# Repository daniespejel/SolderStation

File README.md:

# Solderstation

Barebones Atmega328 based Soldering station  
Firmware: https://github.com/fngstudios/SolderStation_Software

## Features  
*FTDI/Arduino programming port     
*Common soldering tip (with thermocouple) compatible  
*Uses MAX31856 for TC reading  
*Configurable TC type supports J,K,N,E,etc  
*Configurable LCD contrast  
*PID control Kp,Ki and Kd configurable via UI  
*Idle mode for longer tip life  
*Automatic switch-off  
*Arduino compatible 100% customizable  
*Uses any PSU up to 35v like common laptop PSUs (depends on your tip)  
*Can be used barebones (with no cabinet) or built inside custom cabinet  

## Images

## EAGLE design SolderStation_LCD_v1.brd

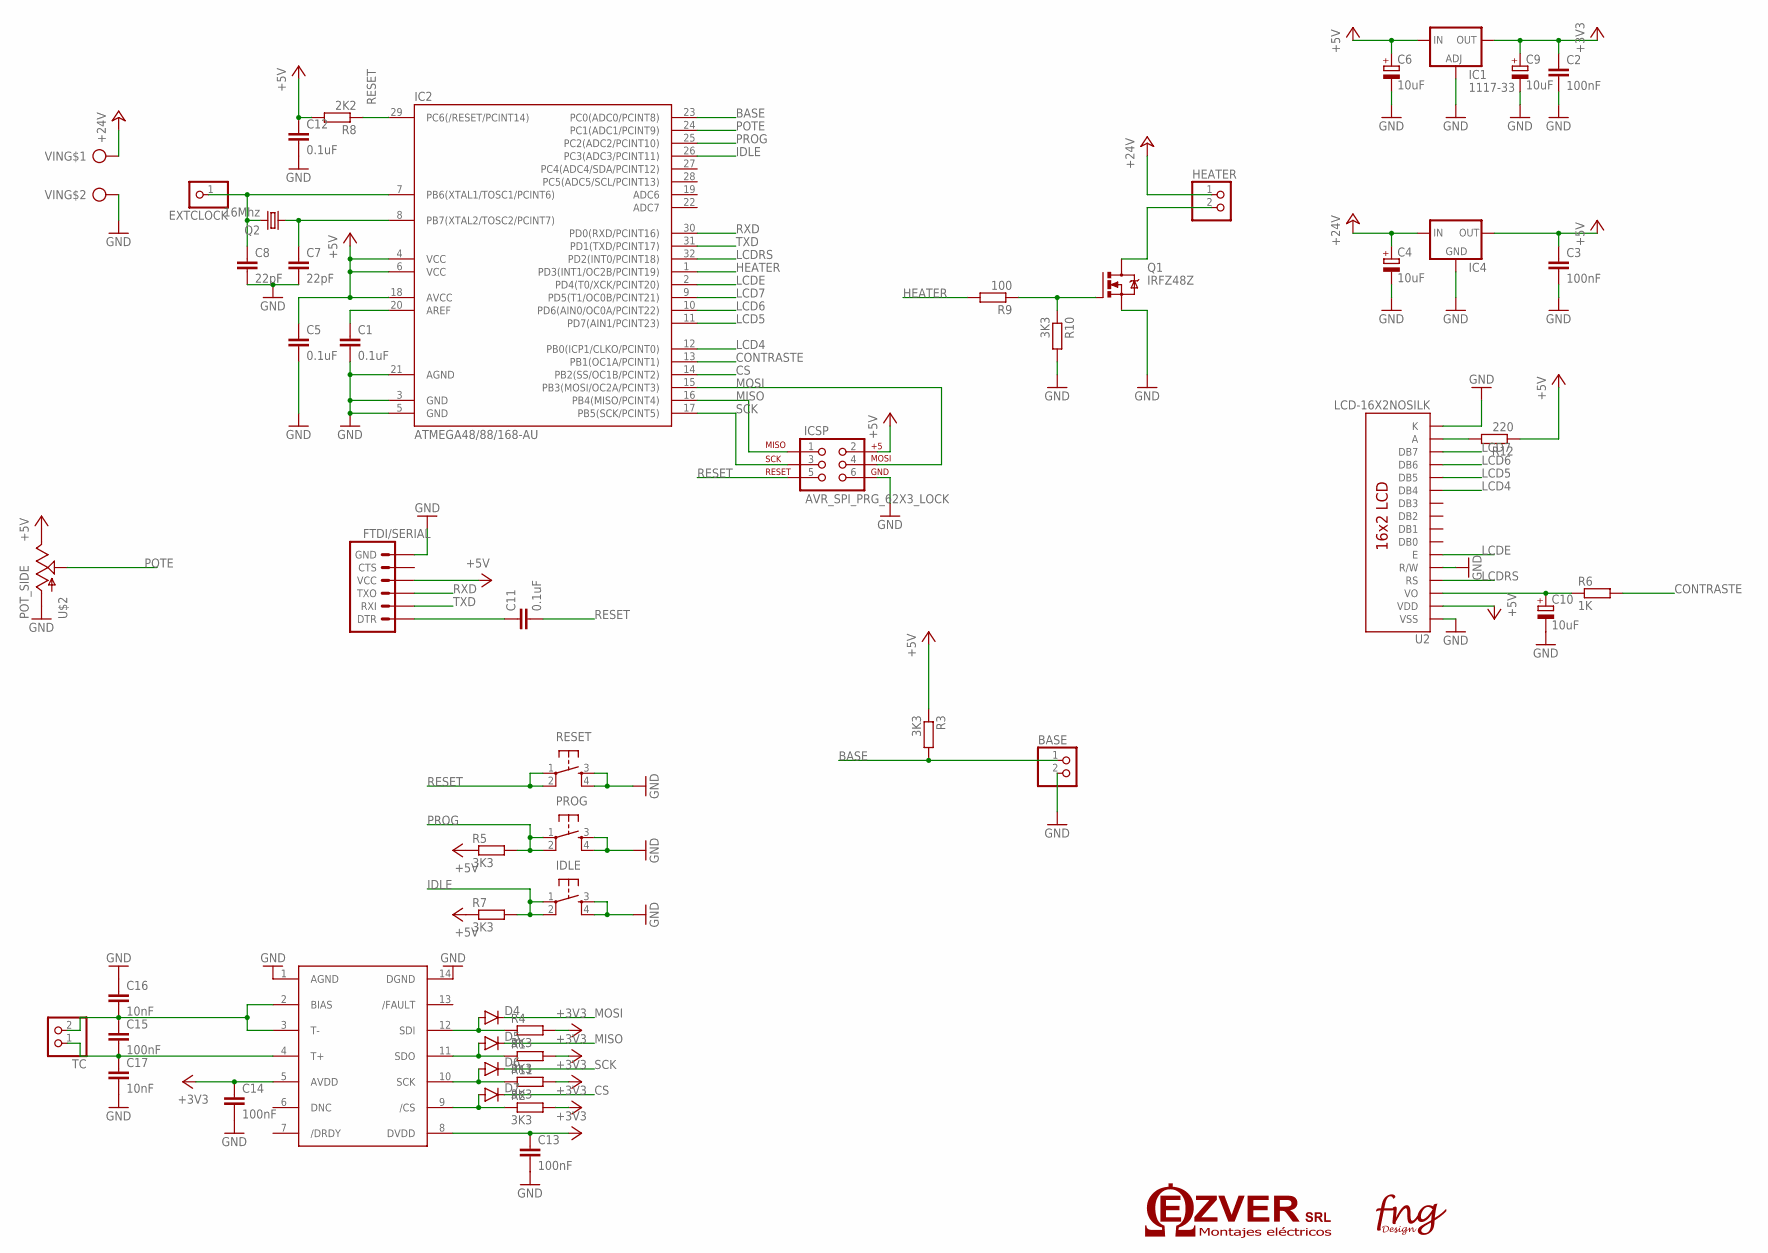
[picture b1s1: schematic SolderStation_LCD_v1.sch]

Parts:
BASE: PINHD-1X2; 1X02
C1, C5, C11, C12: 0.1uF; C1206K
C2, C3, C13, C14, C15: 100nF; C1206K
C4, C6, C9, C10: 10uF; CT3528
C7, C8: 22pF; C1206K
C16, C17: 10nF; C1206K
D4, D5, D6, D7: DIODESOD123; SOD-123
EXTCLOCK: PINHD-1X1; 1X01
FTDI/SERIAL: ARDUINO_SERIAL_PROGRAMLOCK; 1X06_LOCK
HEATER: PINHD-1X2; 1X02
IC1: 1117-33; DPACK
IC2: ATMEGA48/88/168-AU; TQFP32-08
IC4: 78XXL
ICSP: AVR_SPI_PRG_62X3_LOCK; 2X3_LOCK
IDLE: TAC_SWITCHPTH; TACTILE-PTH
PROG: TAC_SWITCHPTH; TACTILE-PTH
Q1: IRFZ48Z; TO220BH
Q2: 16Mhz; HC49U70
R1, R2, R3, R4, R5, R7, R10, R11: 3K3; M1206
R6: 1K; M1206
R8: 2K2; M1206
R9: 100; M1206
R12: 220; M1206
RESET: TAC_SWITCHPTH; TACTILE-PTH
TC: PINHD-1X2; 1X02
TC1: MAX31856; TSSOP-14
U2: LCD-16X2NOSILK; LCD-16X2_NOSILK
U$2: POT_SIDE; POT_ALPHA_SIDE
VIN: CON2

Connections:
+3V3: C2.1, C9.+, C13.1, C14.1, IC1.4 (OUT), R1.2, R2.2, R4.2, R11.2, TC1.5 (AVDD), TC1.8 (DVDD)
+5V: C3.1, C5.1, C6.+, C12.1, FTDI/SERIAL.4 (VCC), IC1.3 (IN), IC2.4 (VCC), IC2.6 (VCC), IC2.18 (AVCC), IC4.OUT, ICSP.2, R3.1, R5.1, R7.1, R8.2, R12.1, U2.2 (VDD), U$2.3 (E)
+24V: C4.+, HEATER.1, IC4.IN, VIN.1
BASE: BASE.1, IC2.23 (PC0(ADC0/PCINT8)), R3.2
CONTRASTE: IC2.13 (PB1(OC1A/PCINT1)), R6.2
CS: D7.C, IC2.14 (PB2(SS/OC1B/PCINT2))
GND: BASE.2, C1.2, C2.2, C3.2, C4.-, C5.2, C6.-, C7.2, C8.2, C9.-, C10.-, C12.2, C13.2, C14.2, C16.1, C17.2, FTDI/SERIAL.6 (GND), IC1.1 (ADJ), IC2.3 (GND), IC2.5 (GND), IC2.21 (AGND), IC4.GND, ICSP.6, IDLE.3, IDLE.4, PROG.3, PROG.4, Q1.S, R10.2, RESET.3, RESET.4, TC1.1 (AGND), TC1.14 (DGND), U2.1 (VSS), U2.5 (R/W), U2.16 (K), U$2.1 (A), VIN.2
HEATER: IC2.1 (PD3(INT1/OC2B/PCINT19)), R9.2
IDLE: IC2.26 (PC3(ADC3/PCINT11)), IDLE.1, IDLE.2, R7.2
LCD4: IC2.12 (PB0(ICP1/CLKO/PCINT0)), U2.11 (DB4)
LCD5: IC2.11 (PD7(AIN1/PCINT23)), U2.12 (DB5)
LCD6: IC2.10 (PD6(AIN0/OC0A/PCINT22)), U2.13 (DB6)
LCD7: IC2.9 (PD5(T1/OC0B/PCINT21)), U2.14 (DB7)
LCDE: IC2.2 (PD4(T0/XCK/PCINT20)), U2.6 (E)
LCDRS: IC2.32 (PD2(INT0/PCINT18)), U2.4 (RS)
MISO: D5.C, IC2.16 (PB4(MISO/PCINT4)), ICSP.1
MOSI: D4.C, IC2.15 (PB3(MOSI/OC2A/PCINT3)), ICSP.4
unnamed: Q1.G, R9.1, R10.1
unnamed: D7.A, R2.1, TC1.9 (/CS)
unnamed: D6.A, R11.1, TC1.10 (SCK)
unnamed: D5.A, R1.1, TC1.11 (SDO)
unnamed: HEATER.2, Q1.D
unnamed: D4.A, R4.1, TC1.12 (SDI)
unnamed: C7.1, IC2.8 (PB7(XTAL2/TOSC2/PCINT7)), Q2.1
unnamed: C10.+, R6.1, U2.3 (VO)
unnamed: C8.1, EXTCLOCK.1, IC2.7 (PB6(XTAL1/TOSC1/PCINT6)), Q2.2
unnamed: C1.1, IC2.20 (AREF)
unnamed: R12.2, U2.15 (A)
unnamed: C11.1, FTDI/SERIAL.1 (DTR)
unnamed: C15.2, C17.1, TC.1, TC1.4 (T+)
unnamed: C15.1, C16.2, TC.2, TC1.2 (BIAS), TC1.3 (T-)
POTE: IC2.24 (PC1(ADC1/PCINT9)), U$2.2 (S)
PROG: IC2.25 (PC2(ADC2/PCINT10)), PROG.1, PROG.2, R5.2
RESET: C11.2, IC2.29 (PC6(/RESET/PCINT14)), ICSP.5, R8.1, RESET.1, RESET.2
RXD: FTDI/SERIAL.3 (TXO), IC2.30 (PD0(RXD/PCINT16))
SCK: D6.C, IC2.17 (PB5(SCK/PCINT5)), ICSP.3
TXD: FTDI/SERIAL.2 (RXI), IC2.31 (PD1(TXD/PCINT17))

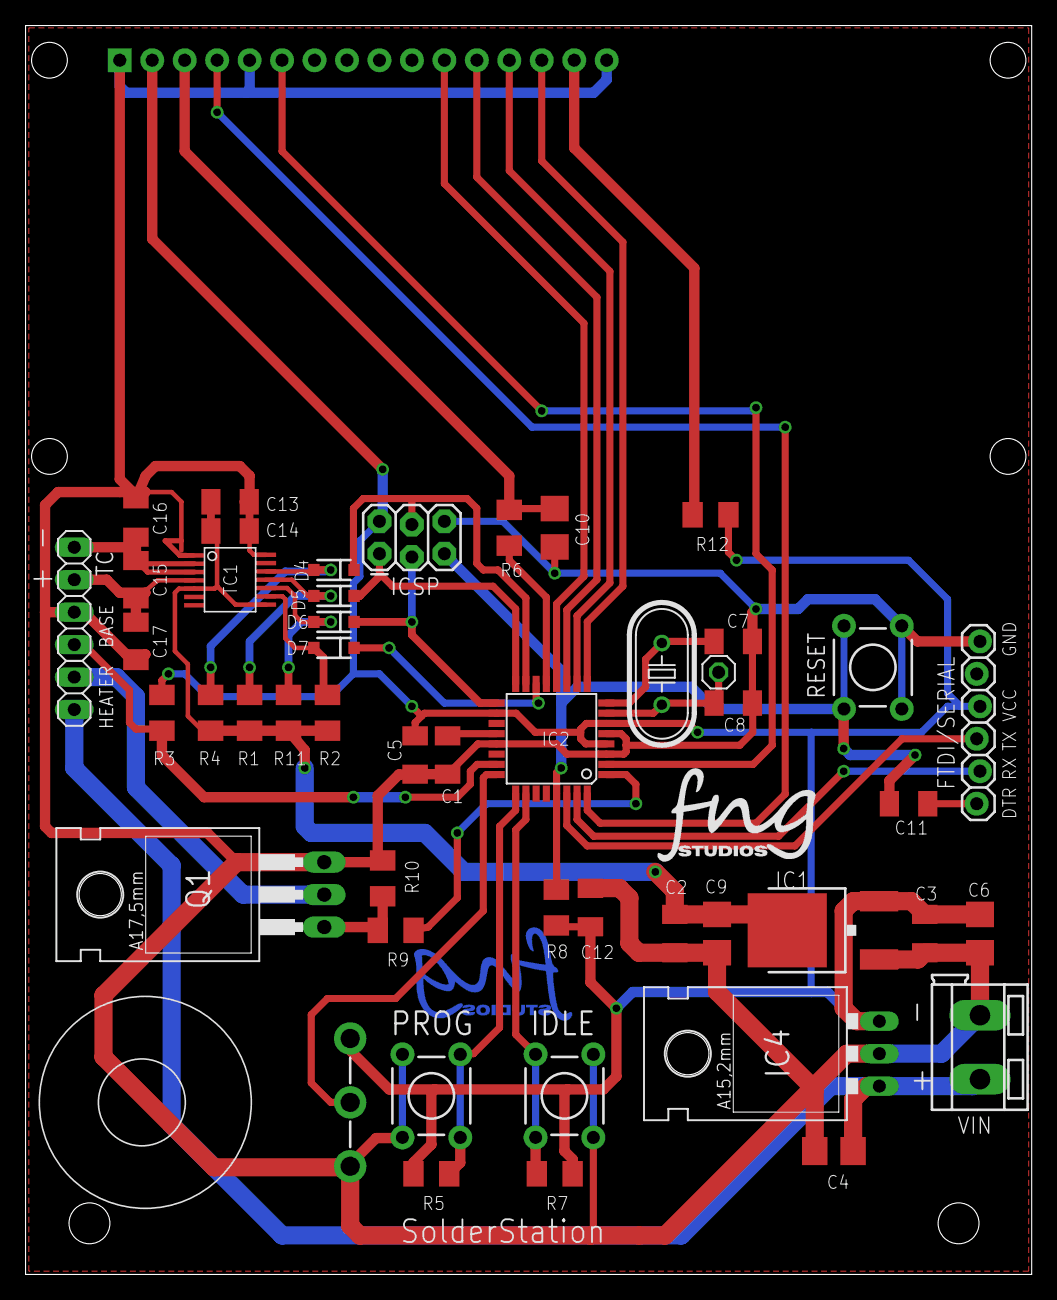
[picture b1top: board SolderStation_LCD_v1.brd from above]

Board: 2 copper layers, 78.7 x 97.7 mm, 53 parts (1 on the bottom side), 37 nets.

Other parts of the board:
U$4: LOGOFNG
U$5: LOGOFNGNAME1

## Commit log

2016-07-07 :space_invader: Added .gitattributes & .gitignore files
2016-12-18 Initial Release
2016-12-18 Readme

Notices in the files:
parts and their libraries:
SparkFun-DiscreteSemi: Licensing: CC v3.0 Share-Alike You are welcome to use this library for commercial purposes.
SparkFun-Electromechanical: Licensing: Creative Commons ShareAlike 4.0 International - https://creativecommons.org/licenses/by-sa/4.0
